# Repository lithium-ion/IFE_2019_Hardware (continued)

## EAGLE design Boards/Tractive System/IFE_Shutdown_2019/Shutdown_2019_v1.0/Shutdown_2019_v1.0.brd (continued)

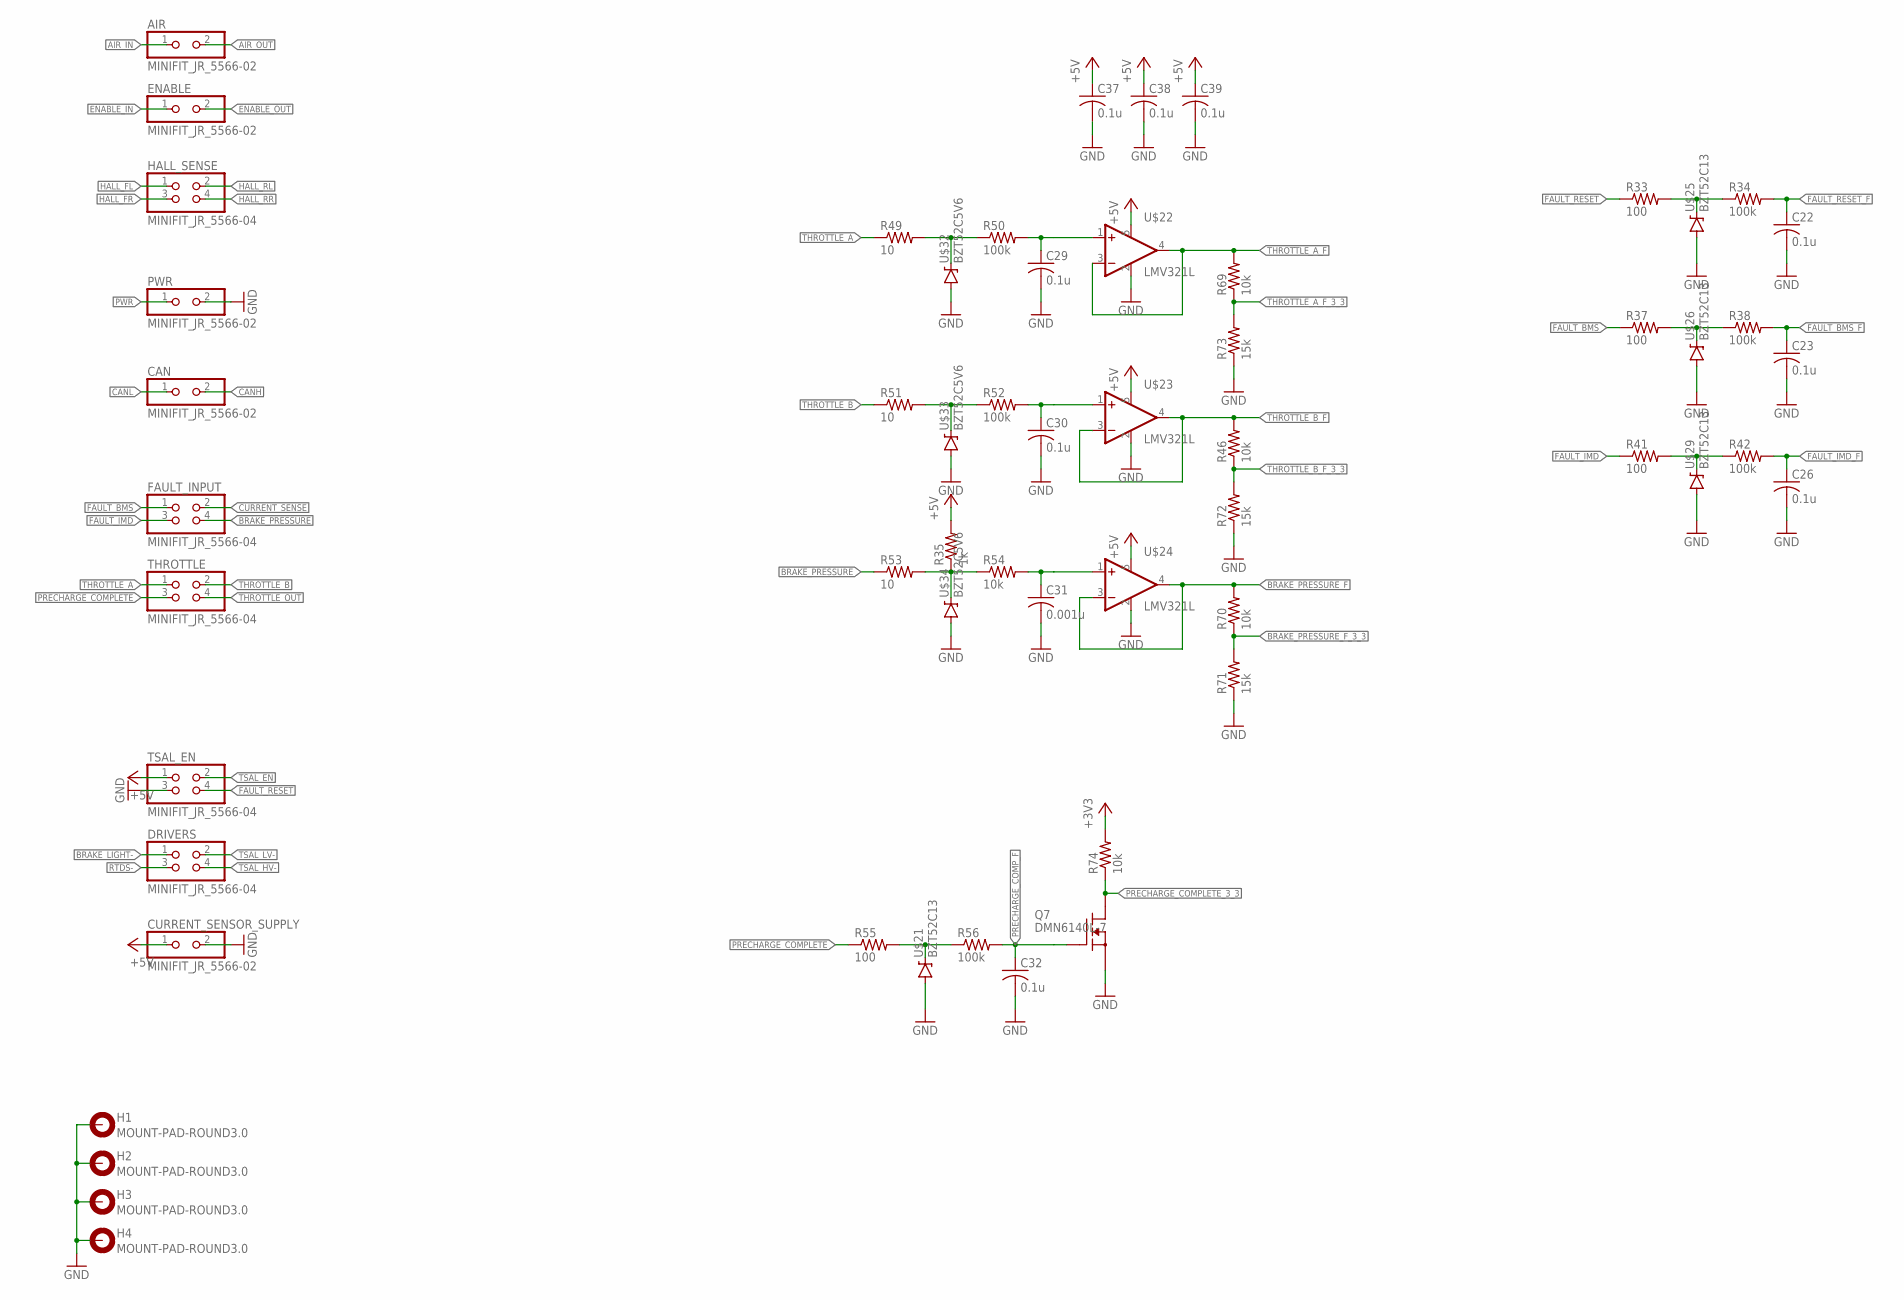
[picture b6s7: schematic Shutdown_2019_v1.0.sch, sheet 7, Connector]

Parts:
AIR: MINIFIT_JR_5566-02
C22, C23, C26, C29, C30, C32: 0.1u; C0805
C31: 0.001u; C0805
C37, C38, C39: 0.1u; C0603
CAN: MINIFIT_JR_5566-02
CURRENT_SENSOR_SUPPLY: MINIFIT_JR_5566-02
DRIVERS: MINIFIT_JR_5566-04
ENABLE: MINIFIT_JR_5566-02
FAULT_INPUT: MINIFIT_JR_5566-04
H1, H2, H3, H4: MOUNT-PAD-ROUND3.0; 3,0-PAD
HALL_SENSE: MINIFIT_JR_5566-04
PWR: MINIFIT_JR_5566-02
Q7: DMN6140L-7; SOT23
R33, R37, R41, R55: 100; R0603
R34, R38, R42, R50, R52, R56: 100k; R0603
R35: 1k; R0603
R46, R54, R69, R70, R74: 10k; R0603
R49, R51, R53: 10; R0603
R71, R72, R73: 15k; R0603
THROTTLE: MINIFIT_JR_5566-04
TSAL_EN: MINIFIT_JR_5566-04
U$21, U$25, U$26, U$29: BZT52C13; SOD-123
U$22, U$23, U$24: LMV321L; SOT23-5
U$32, U$33, U$34: BZT52C5V6; SOD-123

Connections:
+3V3: R74.2; also elsewhere on the board
+5V: C37.1, C38.1, C39.1, CURRENT_SENSOR_SUPPLY.1, R35.2, TSAL_EN.1, U$22.5 (VDD), U$23.5 (VDD), U$24.5 (VDD); also elsewhere on the board
AIR_IN: AIR.1; also elsewhere on the board
AIR_OUT: AIR.2; also elsewhere on the board
BRAKE_LIGHT-: DRIVERS.1; also elsewhere on the board
BRAKE_PRESSURE: FAULT_INPUT.4, R53.1
BRAKE_PRESSURE_F: R70.2, U$24.3 (-IN), U$24.4 (OUT); also elsewhere on the board
BRAKE_PRESSURE_F_3_3: R70.1, R71.2; also elsewhere on the board
CANH: CAN.2; also elsewhere on the board
CANL: CAN.1; also elsewhere on the board
CURRENT_SENSE: FAULT_INPUT.2; also elsewhere on the board
ENABLE_IN: ENABLE.1; also elsewhere on the board
ENABLE_OUT: ENABLE.2; also elsewhere on the board
FAULT_BMS: FAULT_INPUT.1, R37.1
FAULT_BMS_F: C23.1, R38.2; also elsewhere on the board
FAULT_IMD: FAULT_INPUT.3, R41.1
FAULT_IMD_F: C26.1, R42.2; also elsewhere on the board
FAULT_RESET: R33.1, TSAL_EN.4
FAULT_RESET_F: C22.1, R34.2; also elsewhere on the board
GND: C22.2, C23.2, C26.2, C29.2, C30.2, C31.2, C32.2, C37.2, C38.2, C39.2, CURRENT_SENSOR_SUPPLY.2, H1.B3,0, H2.B3,0, H3.B3,0, H4.B3,0, PWR.2, Q7.2 (S), R71.1, R72.1, R73.1, TSAL_EN.3, U$21.A, U$22.2 (GND), U$23.2 (GND), U$24.2 (GND), U$25.A, U$26.A, U$29.A, U$32.A, U$33.A, U$34.A; also elsewhere on the board
HALL_FL: HALL_SENSE.1; also elsewhere on the board
HALL_FR: HALL_SENSE.3; also elsewhere on the board
HALL_RL: HALL_SENSE.2; also elsewhere on the board
HALL_RR: HALL_SENSE.4; also elsewhere on the board
unnamed: R55.2, R56.1, U$21.C
unnamed: R49.2, R50.1, U$32.C
unnamed: R33.2, R34.1, U$25.C
unnamed: R37.2, R38.1, U$26.C
unnamed: C29.1, R50.2, U$22.1 (+IN)
unnamed: R41.2, R42.1, U$29.C
unnamed: R51.2, R52.1, U$33.C
unnamed: C30.1, R52.2, U$23.1 (+IN)
unnamed: R35.1, R53.2, R54.1, U$34.C
unnamed: C31.1, R54.2, U$24.1 (+IN)
PRECHARGE_COMPLETE: R55.1, THROTTLE.3
PRECHARGE_COMPLETE_3_3: Q7.3 (D), R74.1; also elsewhere on the board
PRECHARGE_COMP_F: C32.1, Q7.1 (G), R56.2
PWR: PWR.1; also elsewhere on the board
RTDS-: DRIVERS.3; also elsewhere on the board
THROTTLE_A: R49.1, THROTTLE.1
THROTTLE_A_F: R69.2, U$22.3 (-IN), U$22.4 (OUT); also elsewhere on the board
THROTTLE_A_F_3_3: R69.1, R73.2; also elsewhere on the board
THROTTLE_B: R51.1, THROTTLE.2
THROTTLE_B_F: R46.2, U$23.3 (-IN), U$23.4 (OUT)
THROTTLE_B_F_3_3: R46.1, R72.2; also elsewhere on the board
THROTTLE_OUT: THROTTLE.4; also elsewhere on the board
TSAL_EN: TSAL_EN.2; also elsewhere on the board
TSAL_HV-: DRIVERS.4; also elsewhere on the board
TSAL_LV-: DRIVERS.2; also elsewhere on the board

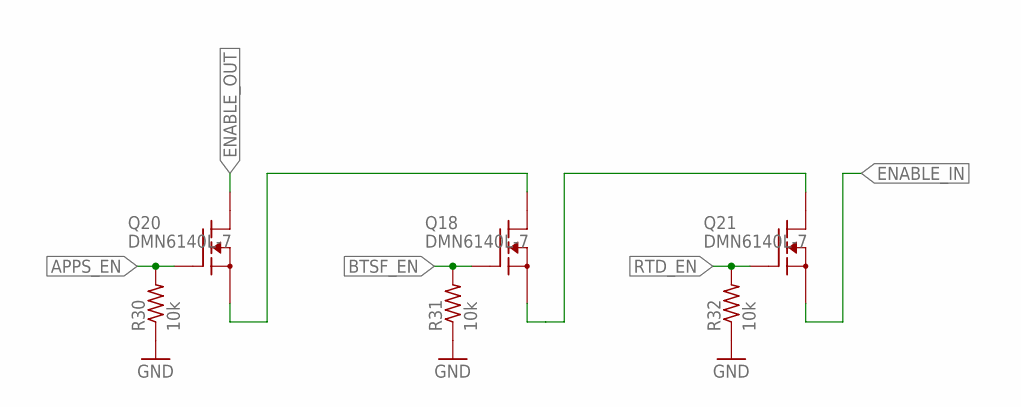
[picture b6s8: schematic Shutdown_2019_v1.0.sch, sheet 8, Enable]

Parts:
Q18, Q20, Q21: DMN6140L-7; SOT23
R30, R31, R32: 10k; R0603

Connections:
APPS_EN: Q20.1 (G), R30.2; also elsewhere on the board
BTSF_EN: Q18.1 (G), R31.2; also elsewhere on the board
ENABLE_IN: Q21.2 (S); also elsewhere on the board
ENABLE_OUT: Q20.3 (D); also elsewhere on the board
GND: R30.1, R31.1, R32.1; also elsewhere on the board
unnamed: Q18.3 (D), Q20.2 (S)
unnamed: Q18.2 (S), Q21.3 (D)
RTD_EN: Q21.1 (G), R32.2; also elsewhere on the board

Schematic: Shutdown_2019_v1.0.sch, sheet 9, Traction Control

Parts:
C16, C20: 1u; C0805
C21: C-USC0603; C0603
C33, C34, C35, C36: 0.001u; C0805
D13: RED; LED-0603
JP2: PINHD-1X5; 1X05
R7: 50k; R0603
R28, R29, R47, R48, R58, R60, R62, R64: 10k; R0603
R57, R59, R61, R63: 10; R0603
R65, R66, R67, R68: 1k; R0603
U2: STM32F103CBT6; QFP50P900X900X160-48N
U$12: MCP4018; SOT23-6
U$18: LMV321L; SOT23-5
U$36, U$37, U$38, U$39: BZT52C5V6; SOD-123

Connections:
!RST_TC: JP2.2, R28.2, U2.7 (NRST)
+3V3: C16.1, C20.1, JP2.1, R28.1, R29.1, U2.9 (VDDA), U2.24 (VDD_1), U2.36 (VDD_2), U2.48 (VDD_3); also elsewhere on the board
+5V: C21.1, R47.1, R48.1, R65.2, R66.2, R67.2, R68.2, U$12.1 (VDD), U$18.5 (VDD); also elsewhere on the board
DEBUG_TC: D13.C, U2.2 (PC13-TAMPER-RTC)
GND: C16.2, C20.2, C21.2, C33.2, C34.2, C35.2, C36.2, JP2.5, R7.1, U2.8 (VSSA), U2.20 (PB2), U2.23 (VSS_1), U2.35 (VSS_2), U2.44 (BOOT0), U2.47 (VSS_3), U$12.2 (VSS), U$18.2 (GND), U$36.A, U$37.A, U$38.A, U$39.A; also elsewhere on the board
HALL_FL: R57.1; also elsewhere on the board
HALL_FL_F: C33.1, R58.2, U2.11 (PA1)
HALL_FR: R59.1; also elsewhere on the board
HALL_FR_F: C34.1, R60.2, U2.10 (PA0-WKUP)
HALL_RL: R61.1; also elsewhere on the board
HALL_RL_F: C35.1, R62.2, U2.12 (PA2)
HALL_RR: R63.1; also elsewhere on the board
HALL_RR_F: C36.1, R64.2, U2.13 (PA3)
unnamed: R7.2, U$12.5 (B), U$18.1 (+IN)
unnamed: D13.A, R29.2
unnamed: R57.2, R58.1, R65.1, U$36.C
unnamed: R59.2, R60.1, R66.1, U$37.C
unnamed: R61.2, R62.1, R67.1, U$38.C
unnamed: R63.2, R64.1, R68.1, U$39.C
PA11: U2.32 (PA11)
SCL_TC: R48.2, U2.42 (PB6), U$12.3 (SCL)
SDA_TC: R47.2, U2.43 (PB7), U$12.4 (SDA)
SPI1_MISO: U2.17 (PA7); also elsewhere on the board
SPI1_MOSI: U2.16 (PA6); also elsewhere on the board
SPI1_NSS: U2.14 (PA4); also elsewhere on the board
SPI1_SCK: U2.15 (PA5); also elsewhere on the board
SWCLK_TC: JP2.4, U2.37 (PA14)
SWDIO_TC: JP2.3, U2.34 (PA13)
THROTTLE_A_F: U$12.6 (W); also elsewhere on the board
THROTTLE_OUT: U$18.3 (-IN), U$18.4 (OUT); also elsewhere on the board

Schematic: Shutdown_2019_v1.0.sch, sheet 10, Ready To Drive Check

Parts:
Q4: DMN6140L-7; SOT23

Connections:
GND: Q4.2 (S); also elsewhere on the board
RTDS-: Q4.3 (D); also elsewhere on the board
RTDS_EN: Q4.1 (G); also elsewhere on the board

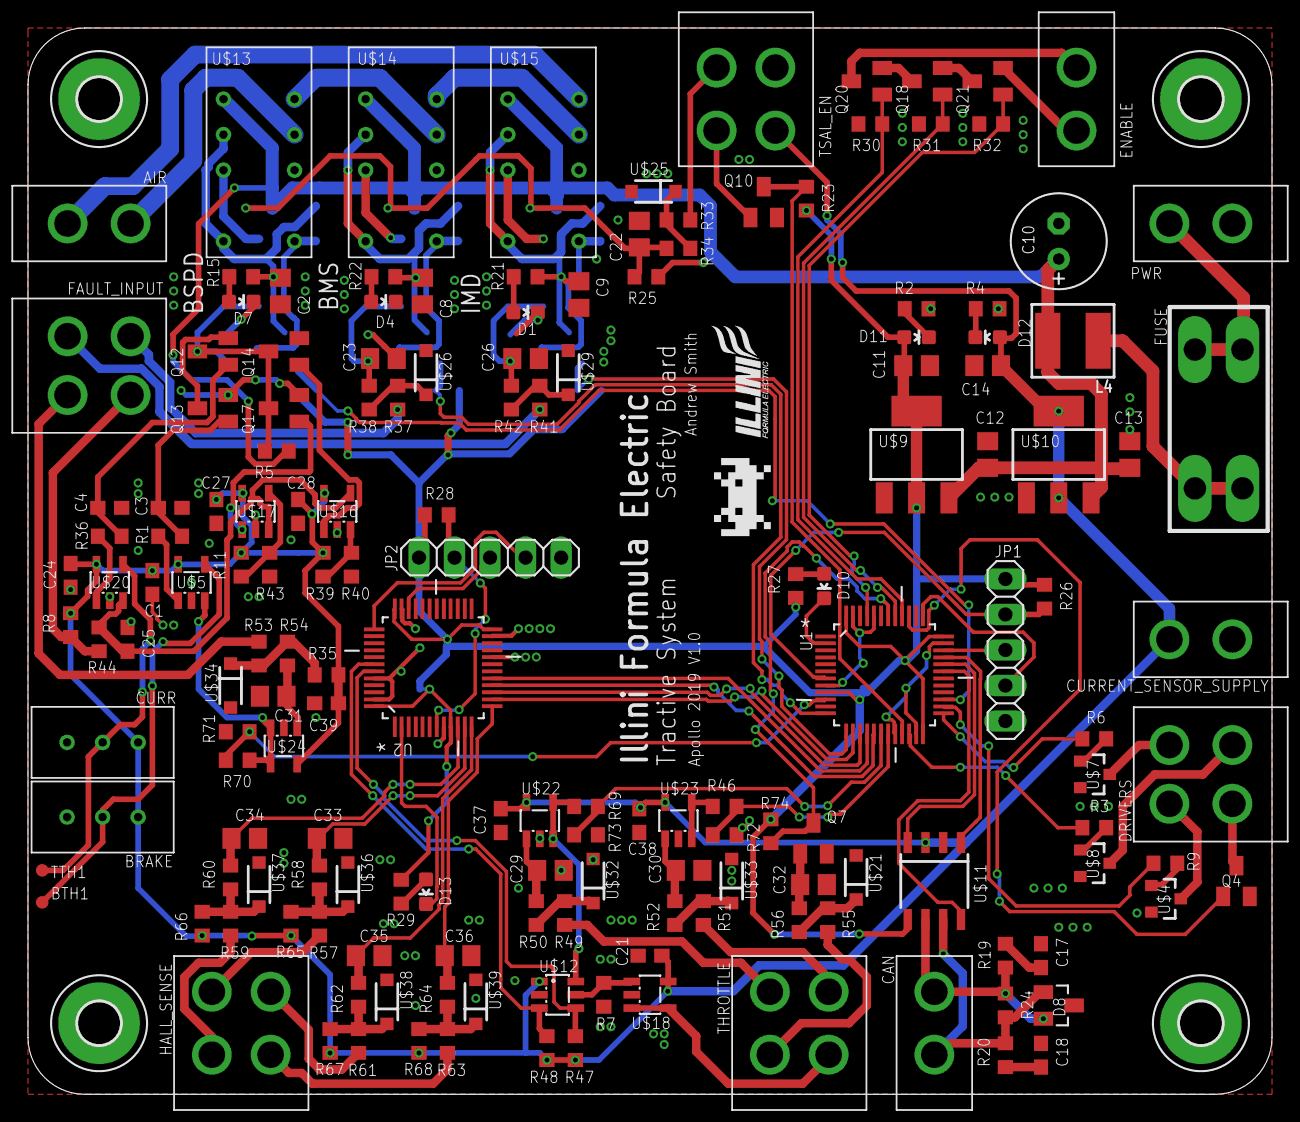
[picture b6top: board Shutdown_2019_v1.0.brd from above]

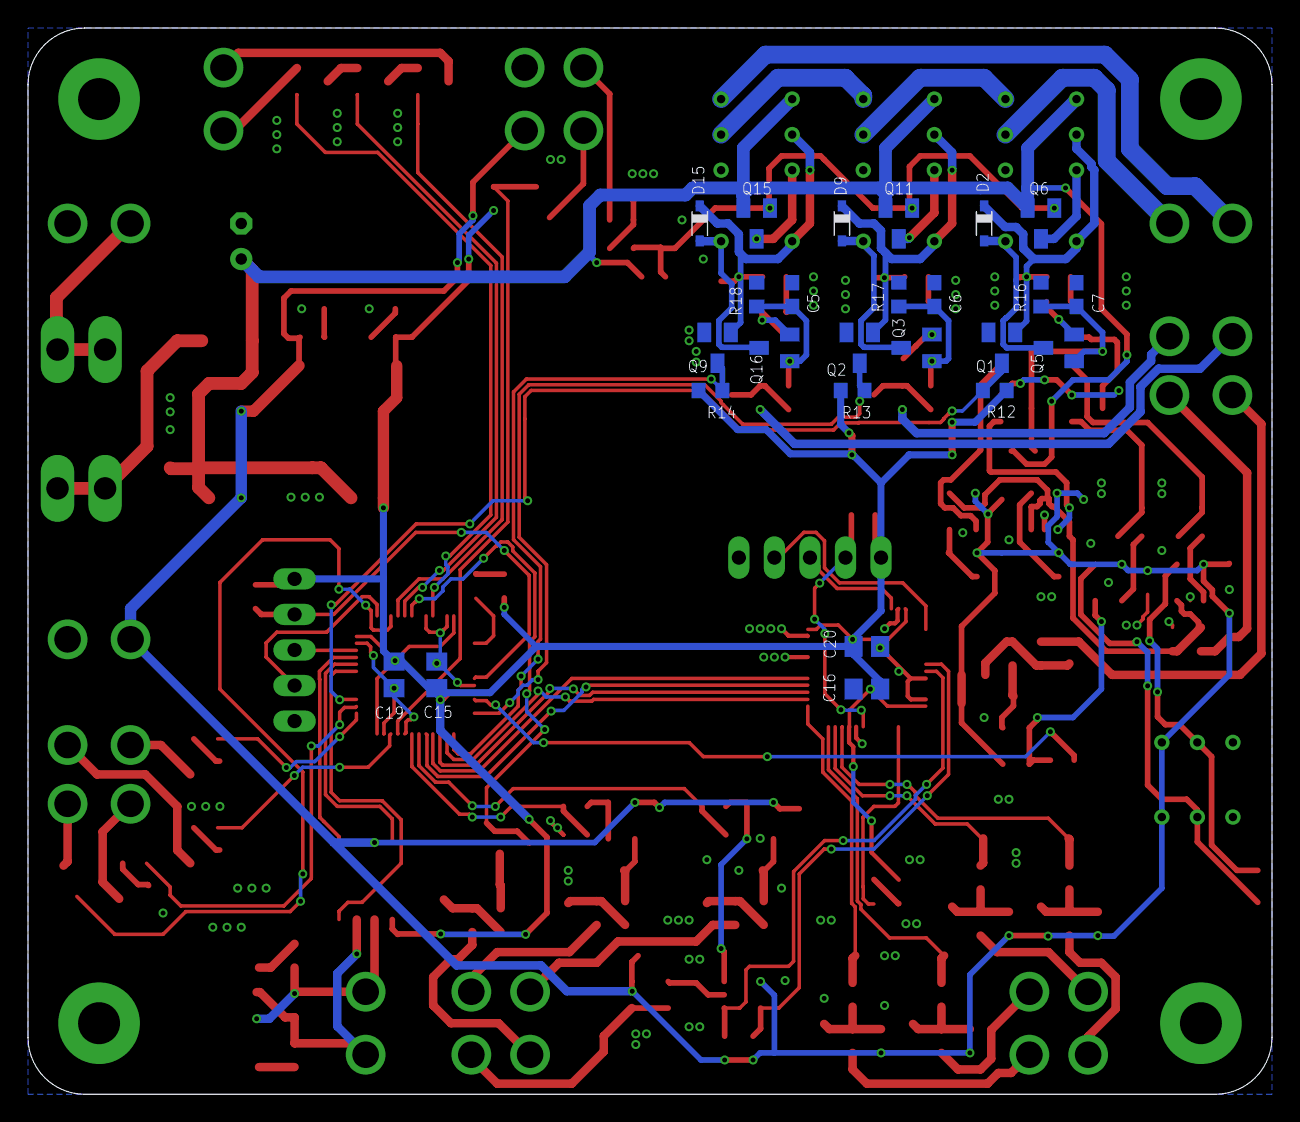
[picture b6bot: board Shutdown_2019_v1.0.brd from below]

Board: 2 copper layers, 88.9 x 76.2 mm, 194 parts (25 on the bottom side), 126 nets.

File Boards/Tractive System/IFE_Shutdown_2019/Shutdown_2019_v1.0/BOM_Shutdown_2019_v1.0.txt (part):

Partlist exported from C:/Users/anges/Documents/IFE/IFE_2019_Hardware/Boards/Tractive System/IFE_Shutdown_2019/Shutdown_2019_v1.0/Shutdown_2019_v1.0.sch at 9/29/2018 3:35 PM

Qty Value              Device             Package                          Parts                                                                                    Description                                                             MPN           OC_FARNELL OC_NEWARK PACKAGE PROD_ID   SPICEPREFIX SUPPLIER           TP_SIGNAL_NAME VALUE
--2                      PINHD-1X5          1X05                             JP1, JP2                                                                                 PIN HEADER                                                                                                                                                                      
--5   0.001u             C-USC0805          C0805                            C31, C33, C34, C35, C36                                                                  CAPACITOR, American symbol                                                                                                   C                                                  
--1   0.01u              C-USC0603          C0603                            C25                                                                                      CAPACITOR, American symbol                                                                                                                                                      
--10  0.1u               C-USC0603          C0603                            C1, C5, C6, C7, C24, C27, C28, C37, C38, C39                                             CAPACITOR, American symbol                                                                                                                                                      
--6   0.1u               C-USC0805          C0805                            C22, C23, C26, C29, C30, C32                                                             CAPACITOR, American symbol                                                                                                   C                                                  
--7   10                 R-US_R0603         R0603                            R49, R51, R53, R57, R59, R61, R63                                                        RESISTOR, American symbol                                                                                                    R                                                  
--8   100                R-US_R0603         R0603                            R2, R4, R19, R20, R33, R37, R41, R55                                                     RESISTOR, American symbol                                                                                                    R                                                  
--2   100k               R-US_R0603         R0603                            R1, R36                                                                                  RESISTOR, American symbol                                                                                                                                                       
--6   100k               R-US_R0603         R0603                            R34, R38, R42, R50, R52, R56                                                             RESISTOR, American symbol                                                                                                    R                                                  
--11  10k                R-US_R0603         R0603                            R5, R8, R12, R13, R14, R16, R17, R18, R23, R39, R43                                      RESISTOR, American symbol                                                                                                                                                       
--18  10k                R-US_R0603         R0603                            R26, R27, R28, R29, R30, R31, R32, R46, R47, R48, R54, R58, R60, R62, R64, R69, R70, R74 RESISTOR, American symbol                                                                                                    R                                                  
--1   10u                INDUCTORNR5040     INDUCTOR_5X5MM_NR5040_NOTHERMALS L4                                                                                       Inductors                                                                                                                                                                       
--3   10uF               C-USC0805          C0805                            C2, C8, C9                                                                               CAPACITOR, American symbol                                                                                                   C                                                  
--1   120                R-US_R0603         R0603                            R24                                                                                      RESISTOR, American symbol                                                                                                    R                                                  
--3   15k                R-US_R0603         R0603                            R71, R72, R73                                                                            RESISTOR, American symbol                                                                                                    R                                                  
--3   1N914              1N914              SOD323-F                         D2, D9, D15                                                                                                                                                                                                                                                              
--4   1k                 R-US_R0603         R0603                            R11, R25, R40, R44                                                                       RESISTOR, American symbol                                                                                                                                                       
--6   1k                 R-US_R0603         R0603                            R9, R35, R65, R66, R67, R68                                                              RESISTOR, American symbol                                                                                                    R                                                  
--1   1u                 C-USC0603          C0603                            C21                                                                                      CAPACITOR, American symbol                                                                                                   C                                                  
--4   1u                 C-USC0805          C0805                            C15, C16, C19, C20                                                                       CAPACITOR, American symbol                                                                                                   C                                                  
--2   2.2u               C-USC0805          C0805                            C11, C14                                                                                 CAPACITOR, American symbol                                                                                                   C                                                  
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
